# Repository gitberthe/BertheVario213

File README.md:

# Projet BertheVario213

Projet d'alti vario gps parapente (avec gestion des TMA CTR..., et mode guidage sol pour randonnée).
- Compatible bluetooth / XCTrack si nécessaire.
- Code C++ Visual Studio/PlateformIO.
- Plateforme Espressif ESP32 Dev Module, LILYGO T5 v2.3.1 GDEM0213T5BN 9102 chip, écran 2.13inch DEPG0213BN, Arduino (processeur 32bits, dual core, 240Mhz).

**La carte avec son pcb :**

**Le schema electrique :**

**Le pcb :**

**La  randonnée :**

mail: spinberthe@gmail.com

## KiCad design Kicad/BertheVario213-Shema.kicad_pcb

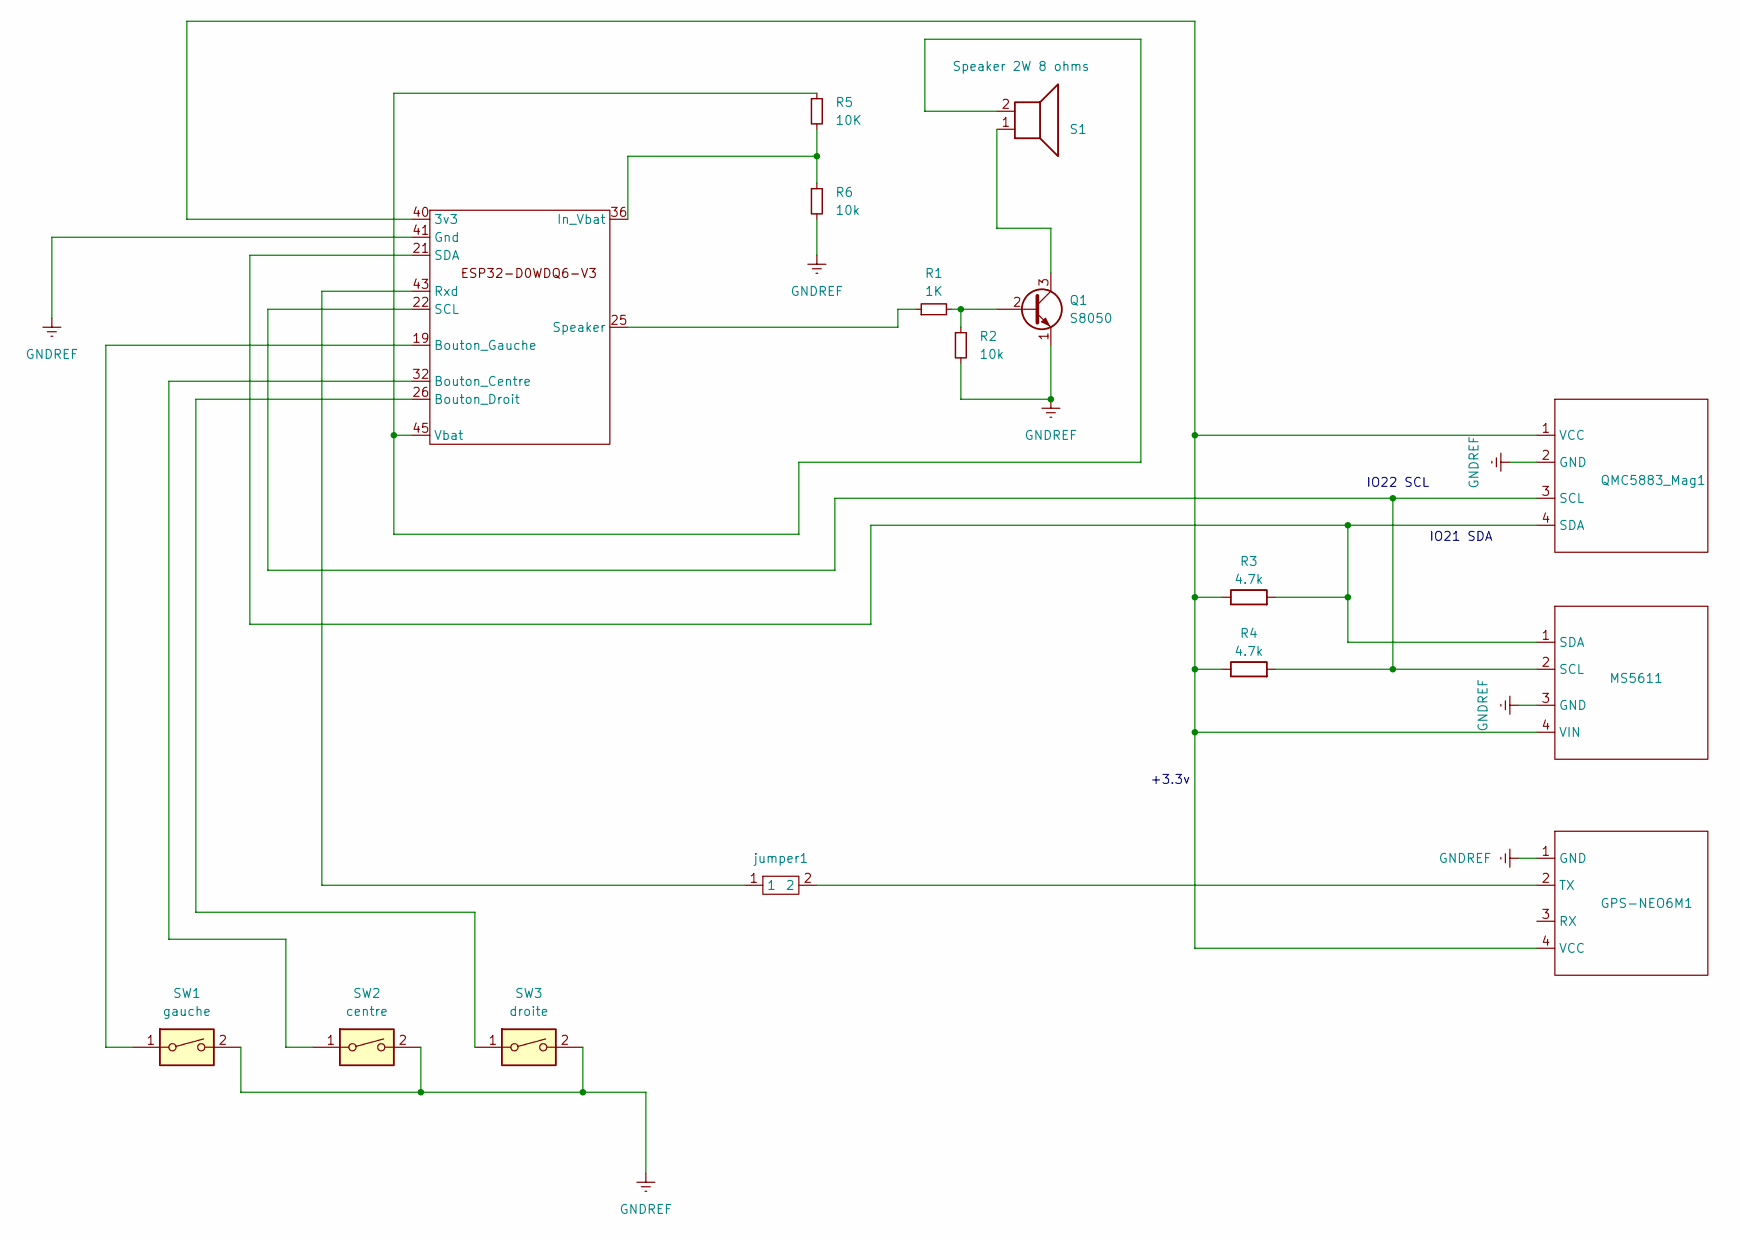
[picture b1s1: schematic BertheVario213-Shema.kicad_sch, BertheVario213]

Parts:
GPS-NEO6M1: -; GPSNEO6V2
MS5611: MS5611
Q1: S8050
QMC5883_Mag1: QMC5883
R1: 1K; R_47
R2, R6: 10k; R_47
R3, R4: 4.7k; R_47
R5: 10K; R_47
S1: Speaker 2W 8 ohms; 2 trous standard
SW1: gauche; switch
SW2: centre; switch
SW3: droite; switch
U1: ESP32-D0WDQ6
jumper1: jumper

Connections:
GNDREF: GPS-NEO6M1.1 (GND), MS5611.3 (GND), Q1.1 (E), QMC5883_Mag1.2 (GND), R2.2, R6.2, SW1.2, SW2.2, SW3.2, U1.41 (Gnd)
unnamed: GPS-NEO6M1.2 (TX), jumper1.2
unnamed: GPS-NEO6M1.4 (VCC), MS5611.4 (VIN), QMC5883_Mag1.1 (VCC), R3.1, R4.1, U1.40 (3v3)
unnamed: MS5611.2 (SCL), QMC5883_Mag1.3 (SCL), R4.2, U1.22 (SCL)
unnamed: MS5611.1 (SDA), QMC5883_Mag1.4 (SDA), R3.2, U1.21 (SDA)
unnamed: Q1.2 (B), R1.2, R2.1
unnamed: Q1.3 (C), S1.1
unnamed: SW2.1, U1.32 (Bouton_Centre)
unnamed: SW3.1, U1.26 (Bouton_Droit)
unnamed: SW1.1, U1.19 (Bouton_Gauche)
unnamed: R5.2, R6.1, U1.36 (In_Vbat)
unnamed: U1.43 (Rxd), jumper1.1
unnamed: R1.1, U1.25 (Speaker)
unnamed: R5.1, S1.2, U1.45 (Vbat)

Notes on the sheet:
IO22 SCL
IO21 SDA
+3.3v

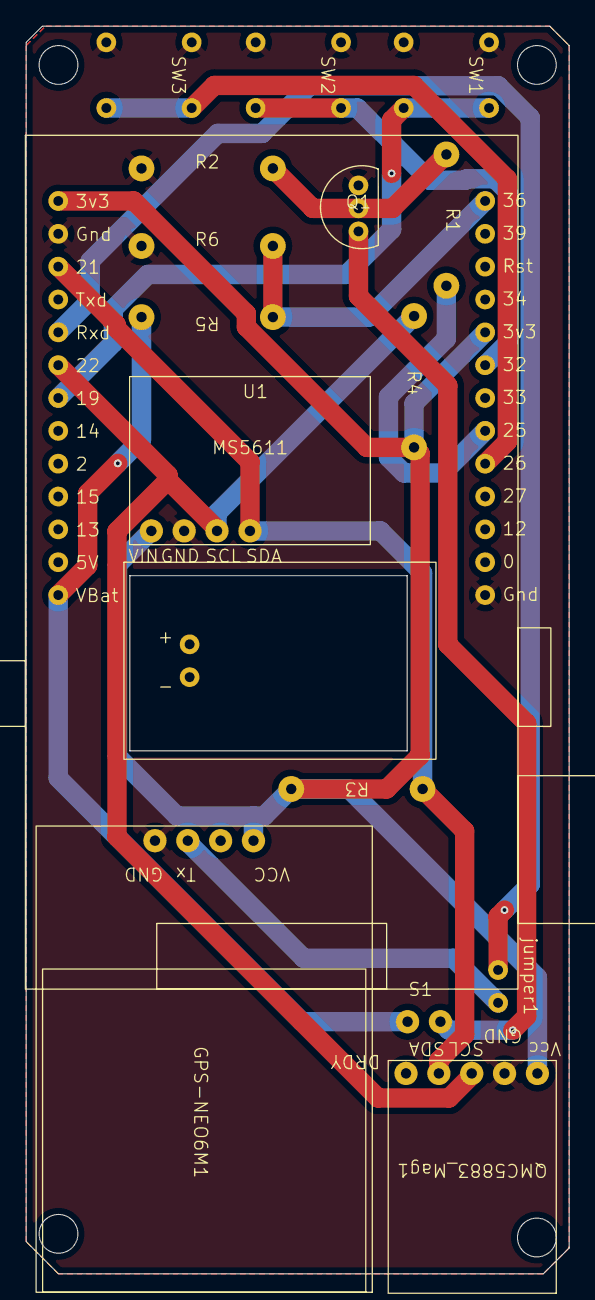
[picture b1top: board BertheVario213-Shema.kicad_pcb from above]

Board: 2 copper layers, 42.0 x 96.5 mm, 16 parts (0 on the bottom side), 14 nets.

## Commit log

2025-02-06 creation
2025-02-06 readme.md
2025-02-06 antenne wifi
2025-02-08 complement doc esp32
2025-02-13 tests carte
2025-02-13 tests carte ok
2025-02-13 progression firmware
2025-02-14 taille ecran
2025-02-14 ihm vz
2025-02-15 FreeCad
2025-02-15 FreeCad Kicad
2025-02-15 pcb Kicad
2025-02-15 empreintes Kicad
2025-02-16 progession pcb
2025-02-16 progression pcb
2025-02-16 doc concepteur
2025-02-16 mise a jour kicad
2025-02-16 son vbat
2025-02-16 shema 1.05
2025-02-16 modif pcb
2025-02-17 capteurs presssion/magnetique
2025-02-17 type ecran
2025-02-17 film uv
2025-02-17 bad async tcp
2025-02-17 bad mqtt
2025-02-18 mail
2025-02-19 bad https
2025-02-19 schema electrique
2025-02-21 pcb pb
2025-02-21 pcb a verifier
2025-02-21 modif ihm
2025-02-22 gps pb
2025-02-23 correction altibarofiltree
2025-02-24 pcb ok a verifier
2025-02-24 shema 1.12
2025-02-24 prix
2025-02-24 photos
2025-02-25 pcb en production
2025-02-25 bug periode tma st-yan
2025-02-25 bug mauvais zonesper.txt
2025-02-25 mise a jour doc
2025-03-02 fichiers de zone
2025-03-19 pcb BV-213 ok
2025-03-20 ota bug gps mag
2025-03-20 page de presentation
2025-03-20 gps magnetique
2025-03-20 documentation
2025-03-20 ota ok
2025-03-21 page Vz
2025-03-21 page sys
2025-03-21 caracteres pages
2025-03-21 freecad esp32
2025-03-21 freecad bas
2025-03-22 zones aeriennes
2025-03-22 bug zone proche
2025-03-22 doc utilisateur
2025-03-22 zone frontiere et rando
2025-03-22 readme.txt rando
2025-03-22 base boitier
